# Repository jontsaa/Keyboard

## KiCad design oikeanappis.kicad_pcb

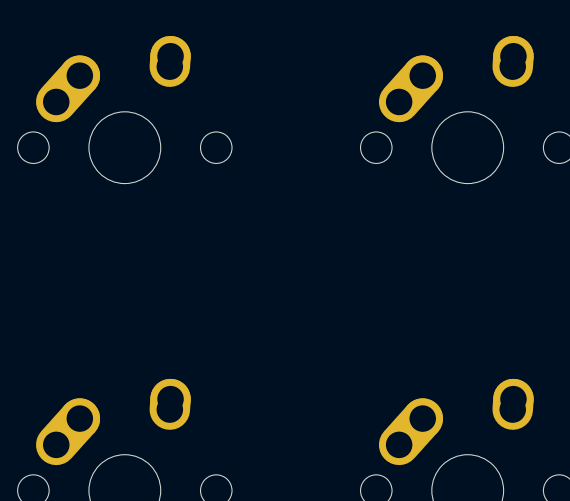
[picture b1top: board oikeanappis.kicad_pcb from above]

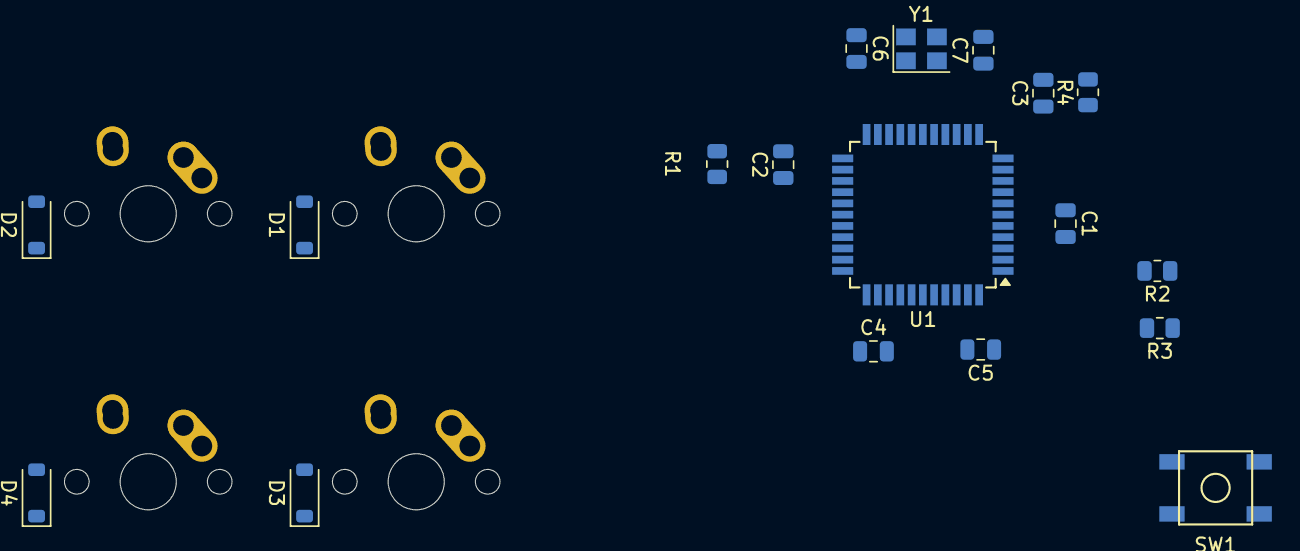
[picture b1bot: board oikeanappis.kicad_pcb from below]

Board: 2 copper layers, 22 parts (18 on the bottom side), 17 nets, no tracks yet.

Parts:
C1: 1uF; C_0805_2012Metric
C2, C3, C4: 0.1uF; C_0805_2012Metric
C5: 10uF; C_0805_2012Metric
C6, C7: 22pF; C_0805_2012Metric
D1, D2, D3, D4: D_Small; D_SOD-123
MX1, MX2, MX3, MX4: MX-NoLED; MX-1U-NoLED
R1, R4: 10k; R_0805_2012Metric
R2, R3: 22; R_0805_2012Metric
SW1: SW_Push; SKQG-1155865
U1: ATmega32U4-A; TQFP-44_10x10mm_P0.8mm
Y1: 16MHz; Crystal_SMD_3225-4Pin_3.2x2.5mm

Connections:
+5V: C2.1, C3.1, C4.1, C5.1, R4.2, U1.2 (UVCC), U1.7 (VBUS), U1.14 (VCC), U1.24 (AVCC), U1.34 (VCC), U1.44 (AVCC)
COL0: MX1.1 (COL), MX3.1 (COL)
COL1: MX2.1 (COL), MX4.1 (COL)
GND: C1.2, C2.2, C3.2, C4.2, C5.2, C6.1, C7.1, R1.2, SW1.1, U1.5 (UGND), U1.15 (GND), U1.23 (GND), U1.35 (GND), U1.43 (GND), Y1.2, Y1.4
unnamed: D1.2 (A), MX1.2 (ROW)
unnamed: D2.2 (A), MX2.2 (ROW)
unnamed: D3.2 (A), MX3.2 (ROW)
unnamed: D4.2 (A), MX4.2 (ROW)
unnamed: R2.2, U1.4 (D+)
unnamed: R3.2, U1.3 (D-)
unnamed: C1.1, U1.6 (UCAP)
unnamed: C6.2, U1.17 (XTAL1), Y1.1
unnamed: C7.2, U1.16 (XTAL2), Y1.3
unnamed: R1.1, U1.33 (~HWB/PE2)
unnamed: R4.1, SW1.2, U1.13 (~RESET)
ROW0: D1.1 (K), D2.1 (K)
ROW1: D3.1 (K), D4.1 (K)
